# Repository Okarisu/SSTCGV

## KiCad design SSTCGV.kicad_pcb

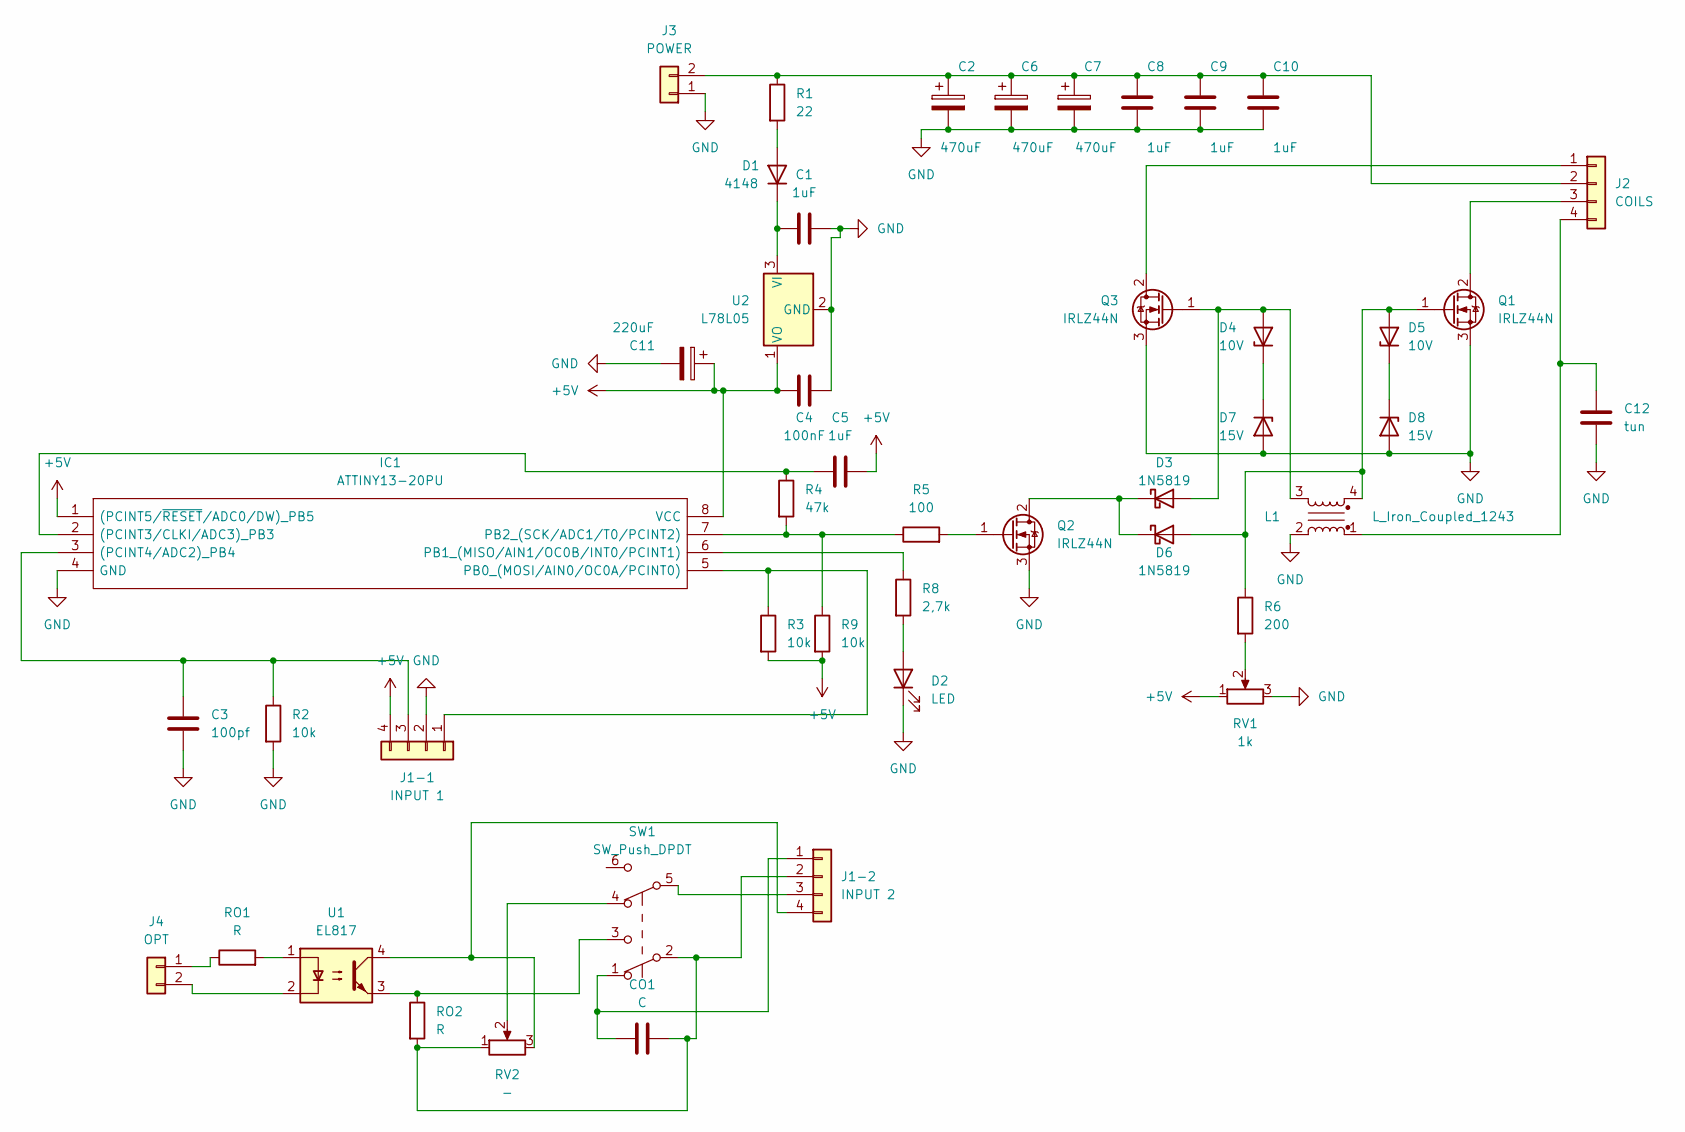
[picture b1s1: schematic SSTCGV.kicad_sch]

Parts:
C1, C5, C8, C9, C10: 1uF; CP_Radial_Tantal_D5.0mm_P2.50mm
C2, C6, C7: 470uF; CP_Radial_Tantal_D5.0mm_P2.50mm
C3: 100pf; CP_Radial_Tantal_D5.0mm_P2.50mm
C4: 100nF; CP_Radial_Tantal_D5.0mm_P2.50mm
C11: 220uF; CP_Radial_Tantal_D5.0mm_P2.50mm
C12: tun; CP_Radial_Tantal_D5.0mm_P2.50mm
CO1: C; CP_Radial_Tantal_D5.0mm_P2.50mm
D1: 4148; D_5KP_P10.16mm_Horizontal
D2: LED; LED_D5.0mm-3_Horizontal_O3.81mm_Z3.0mm
D3, D6: 1N5819; D_5KP_P10.16mm_Horizontal
D4, D5: 10V; D_5KPW_P12.70mm_Horizontal
D7, D8: 15V; D_5KPW_P12.70mm_Horizontal
IC1: ATTINY13-20PU; DIP794W56P254L959H533Q8N; Manufacturer_Part_Number ATTINY13-20PU; Mouser Part Number 556-ATTINY13-20PU
J1-1: INPUT 1; PinSocket_1x04_P2.54mm_Vertical
J1-2: INPUT 2; PinSocket_1x04_P2.54mm_Vertical
J2: COILS; PinSocket_1x04_P2.54mm_Vertical
J3: POWER; PinSocket_1x02_P2.54mm_Vertical
J4: OPT; PinSocket_1x02_P2.54mm_Vertical
L1: L_Iron_Coupled_1243; PinSocket_1x04_P2.54mm_Vertical
Q1, Q2, Q3: IRLZ44N; TO-220-3_Vertical
R1: 22; R_Axial_DIN0411_L9.9mm_D3.6mm_P15.24mm_Horizontal
R2, R3, R9: 10k; R_Axial_DIN0411_L9.9mm_D3.6mm_P15.24mm_Horizontal
R4: 47k; R_Axial_DIN0411_L9.9mm_D3.6mm_P15.24mm_Horizontal
R5: 100; R_Axial_DIN0411_L9.9mm_D3.6mm_P15.24mm_Horizontal
R6: 200; R_Axial_DIN0411_L9.9mm_D3.6mm_P15.24mm_Horizontal
R8: 2,7k; R_Axial_DIN0411_L9.9mm_D3.6mm_P15.24mm_Horizontal
RO1, RO2: R; R_Axial_DIN0411_L9.9mm_D3.6mm_P15.24mm_Horizontal
RV1: 1k; Potentiometer_ACP_CA9-H2,5_Horizontal
RV2: -; Potentiometer_Bourns_3005_Horizontal
SW1: SW_Push_DPDT; SW_Push_2P2T_Toggle_CK_PVA2xxH1xxxxxxV2
U1: EL817; DIP-4_W7.62mm
U2: L78L05; TO-92_Inline

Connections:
+5V: C4.1, C5.2, C11.1, IC1.1 ((PCINT5/~RESET/ADC0/DW)_PB5), IC1.8 (VCC), J1-1.4, R3.2, R9.2, RV1.1, U2.1 (VO)
GND: C1.2, C2.2, C3.2, C4.2, C6.2, C7.2, C8.2, C9.2, C10.2, C11.2, C12.2, D2.1 (K), D7.2 (A), D8.2 (A), IC1.4 (GND), J1-1.2, J3.1, L1.2, Q1.3 (S), Q2.3 (S), Q3.3 (S), R2.2, RV1.3, U2.2 (GND)
unnamed: C2.1, C6.1, C7.1, C8.1, C9.1, C10.1, J2.2, J3.2, R1.1
unnamed: CO1.1, J1-2.1, SW1.1 (A)
unnamed: CO1.2, J1-2.2, RO2.2, RV2.1, SW1.2 (B)
unnamed: C1.1, D1.1 (K), U2.3 (VI)
unnamed: D3.1 (K), D6.1 (K), Q2.2 (D)
unnamed: D4.1 (K), D7.1 (K)
unnamed: D3.2 (A), D4.2 (A), L1.3, Q3.1 (G)
unnamed: D5.2 (A), D6.2 (A), L1.4, Q1.1 (G), R6.1
unnamed: D5.1 (K), D8.1 (K)
unnamed: C3.1, IC1.3 ((PCINT4/ADC2)_PB4), J1-1.3, R2.1
unnamed: J1-2.3, SW1.5 (B)
unnamed: J4.1, RO1.1
unnamed: C12.1, J2.4, L1.1
unnamed: J2.3, Q1.2 (D)
unnamed: Q2.1 (G), R5.2
unnamed: J2.1, Q3.2 (D)
unnamed: D1.2 (A), R1.2
unnamed: IC1.5 (PB0_(MOSI/AIN0/OC0A/PCINT0)), J1-1.1, R3.1
unnamed: C5.1, IC1.2 ((PCINT3/CLKI/ADC3)_PB3), R4.1
unnamed: IC1.7 (PB2_(SCK/ADC1/T0/PCINT2)), R4.2, R5.1, R9.1
unnamed: R6.2, RV1.2
unnamed: IC1.6 (PB1_(MISO/AIN1/OC0B/INT0/PCINT1)), R8.1
unnamed: D2.2 (A), R8.2
unnamed: RV2.2, SW1.4 (A)
unnamed: RO1.2, U1.1
unnamed: J4.2, U1.2
unnamed: RO2.1, SW1.3 (C), U1.3
unnamed: J1-2.4, RV2.3, U1.4

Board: 2 copper layers, 46 parts (0 on the bottom side), 30 nets, no tracks yet.

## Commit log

2022-02-18 schematics done
2022-02-25 corrections of schematics
2022-02-25 woking on pcb
2022-03-03 schematics
2022-03-25 franta scheme approve
2022-07-16 workspace maintance
